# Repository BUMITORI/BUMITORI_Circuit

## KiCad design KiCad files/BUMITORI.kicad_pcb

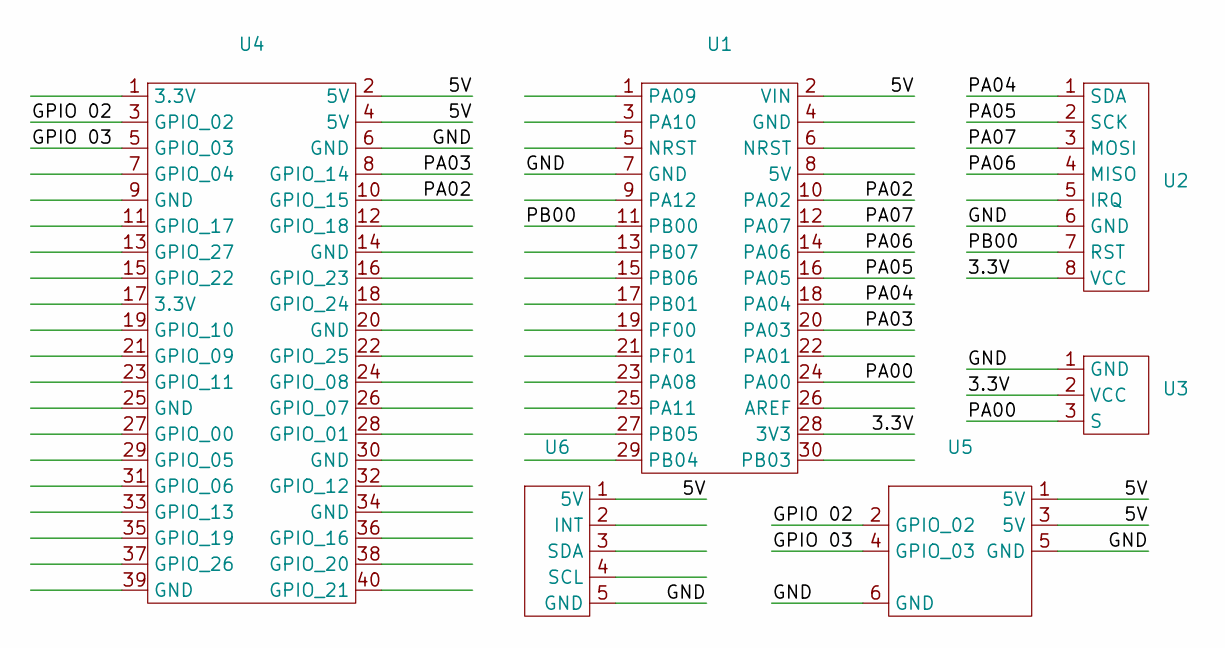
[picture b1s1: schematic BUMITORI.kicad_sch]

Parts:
U1: NUCLEO-F303K8
U2: RC522
U3: PassiveBuzzer
U4: RaspberryPI_4B
U5: RaspberryPI_UPS
U6: RaspberryPI_7inch-Display

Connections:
/3.3V: U1.28 (3V3), U2.8 (VCC), U3.2 (VCC)
/5V: U1.2 (VIN), U4.2 (5V), U4.4 (5V), U5.1 (5V), U5.3 (5V), U6.1 (5V)
/GND: U1.7 (GND), U2.6 (GND), U3.1 (GND), U4.6 (GND), U5.5 (GND), U5.6 (GND), U6.5 (GND)
/GPIO 02: U4.3 (GPIO_02), U5.2 (GPIO_02)
/GPIO 03: U4.5 (GPIO_03), U5.4 (GPIO_03)
/PA00: U1.24 (PA00), U3.3 (S)
/PA02: U1.10 (PA02), U4.10 (GPIO_15)
/PA03: U1.20 (PA03), U4.8 (GPIO_14)
/PA04: U1.18 (PA04), U2.1 (SDA)
/PA05: U1.16 (PA05), U2.2 (SCK)
/PA06: U1.14 (PA06), U2.4 (MISO)
/PA07: U1.12 (PA07), U2.3 (MOSI)
/PB00: U1.11 (PB00), U2.7 (RST)

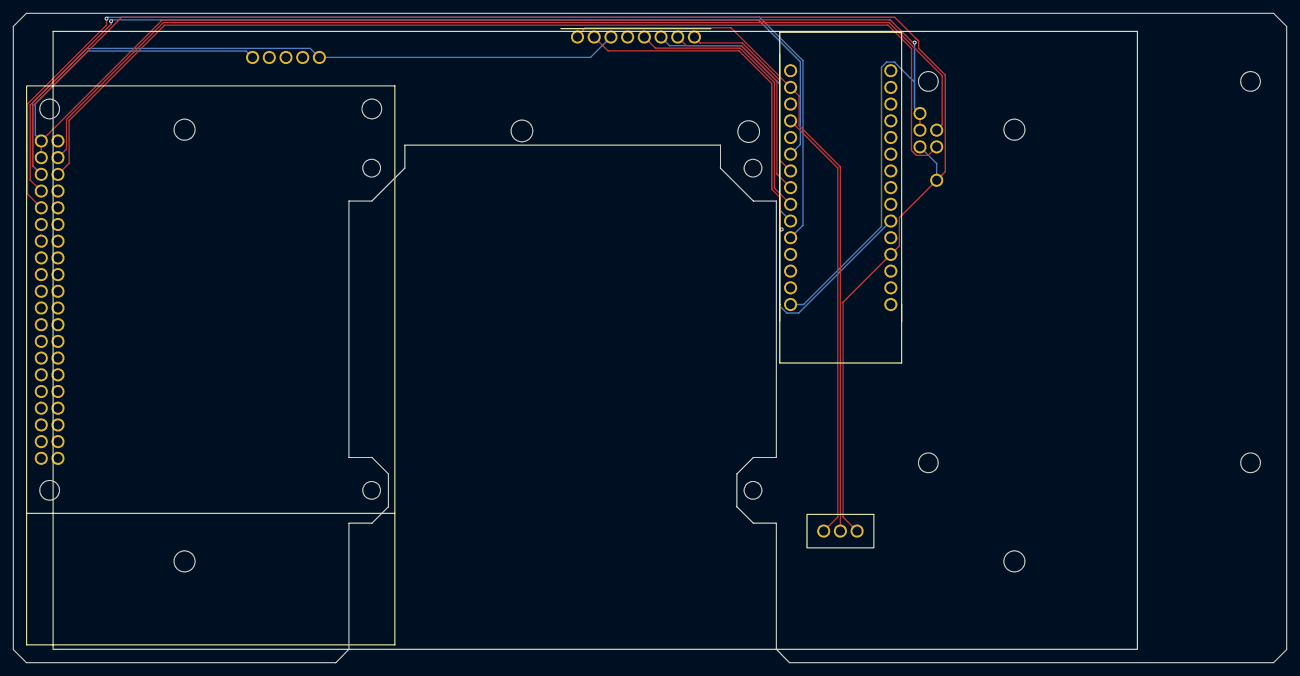
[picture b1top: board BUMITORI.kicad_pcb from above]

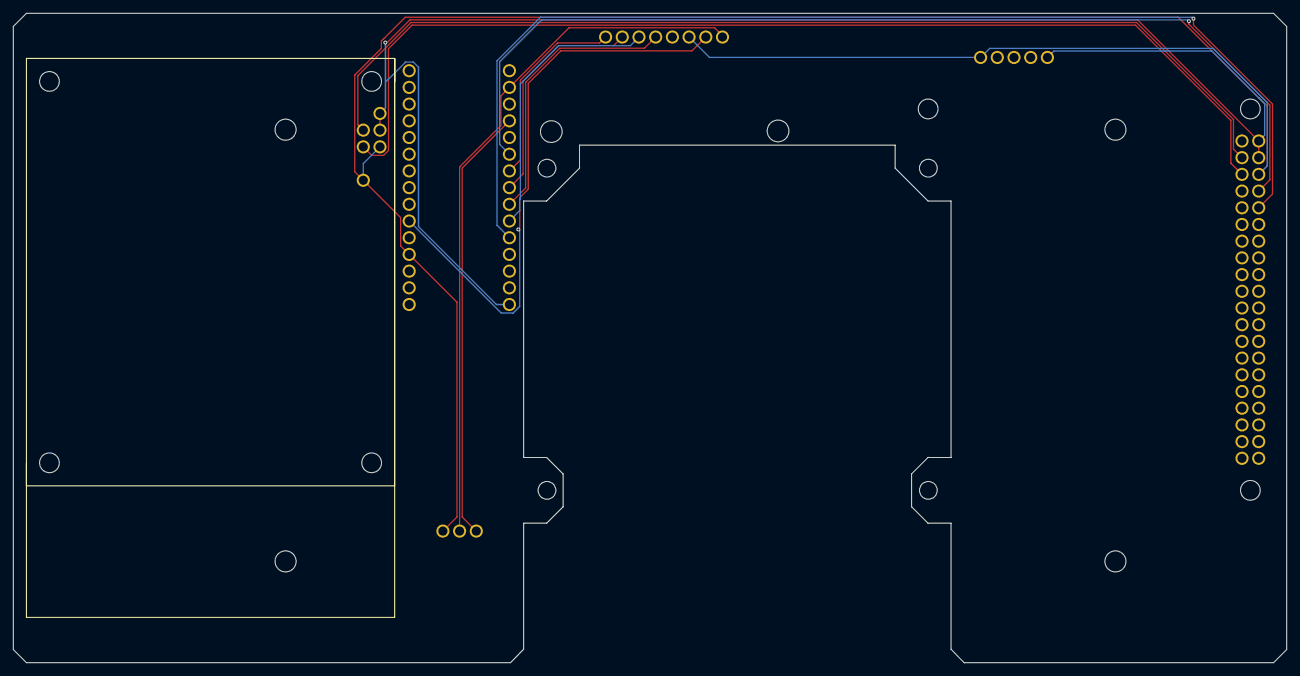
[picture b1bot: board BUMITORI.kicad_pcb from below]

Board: 2 copper layers, 193.6 x 98.8 mm, 6 parts (2 on the bottom side), 13 nets.

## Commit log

2025-01-29 ADD : 회로도 .md 파일
2025-02-18 ADD : TinyCAD Circuit
2025-02-18 ADD : RaspberryPI UPS
2025-02-25 ADD : RaspberryPI 7inch-Display parts
2025-02-25 ADD : KiCad files
2025-02-25 ADD : PCB Gerber file
